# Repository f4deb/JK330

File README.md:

JK330
=====

transceiver 3-30mhz QRP

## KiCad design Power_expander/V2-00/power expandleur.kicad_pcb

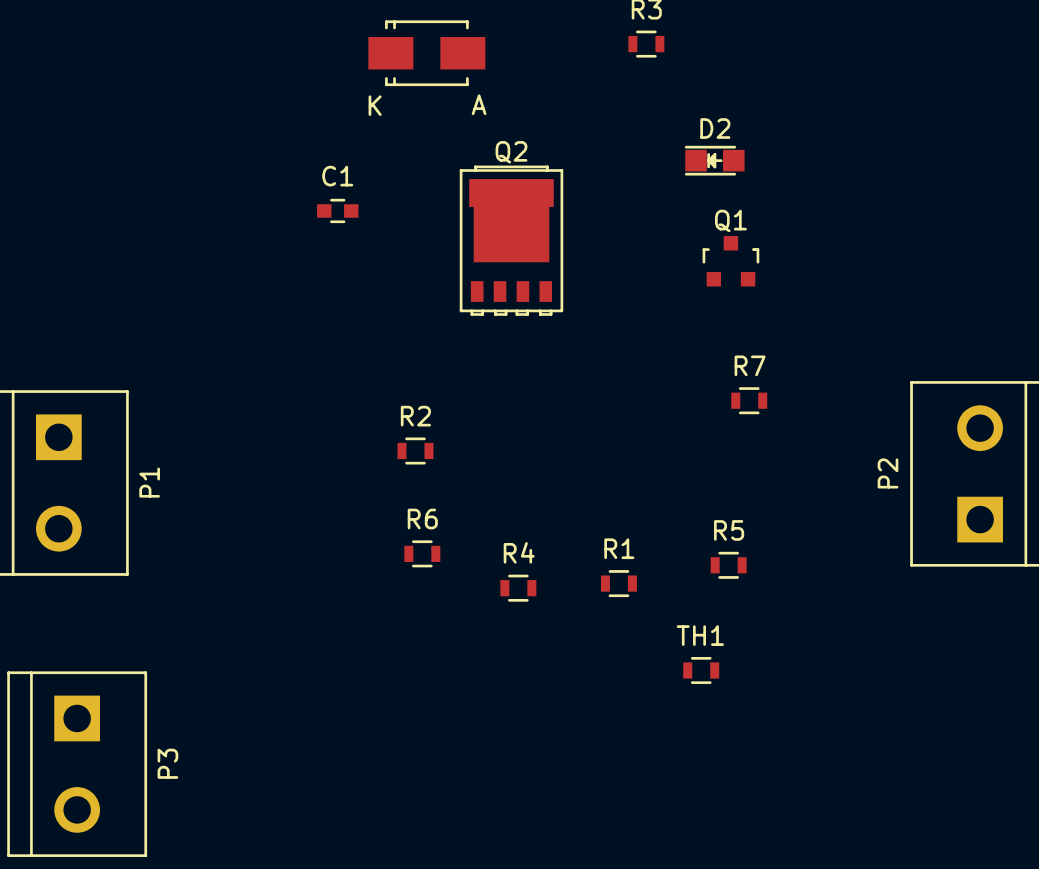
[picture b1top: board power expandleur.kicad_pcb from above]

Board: 2 copper layers, 16 parts (0 on the bottom side), 11 nets, no tracks yet.

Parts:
C1: 100nF; C_0603
D1: ZENERsmall; SMA_Standard
D2: LED; LED_0805
P1, P2, P3: CONN_01X02; bornier2
Q1: Q_NPN_BCE; SOT-23
Q2: Q_NMOS_DGS; SOT-669_LFPAK
R1: 330; R_0603
R2: 100k; R_0603
R3, R5: 1K; R_0603
R4: 10K; R_0603
R6: 4.7K; R_0603
R7: 100K; R_0603
TH1: THERMISTOR 220; R_0603

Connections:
+24V: P1.2, P3.2, R3.1
GND: C1.2, D1.2, D2.1, P1.1, Q1.3, Q2.3, R7.2
unnamed: C1.1, D1.1, R3.2, R4.1, R5.1
unnamed: D2.2, R6.2
unnamed: P2.1, R2.2
unnamed: P2.2, TH1.2
unnamed: P3.1, Q2.1
unnamed: Q1.1, R4.2
unnamed: Q1.2, Q2.2, R5.2, R6.1, R7.1
unnamed: R1.1, R2.1
unnamed: R1.2, TH1.1

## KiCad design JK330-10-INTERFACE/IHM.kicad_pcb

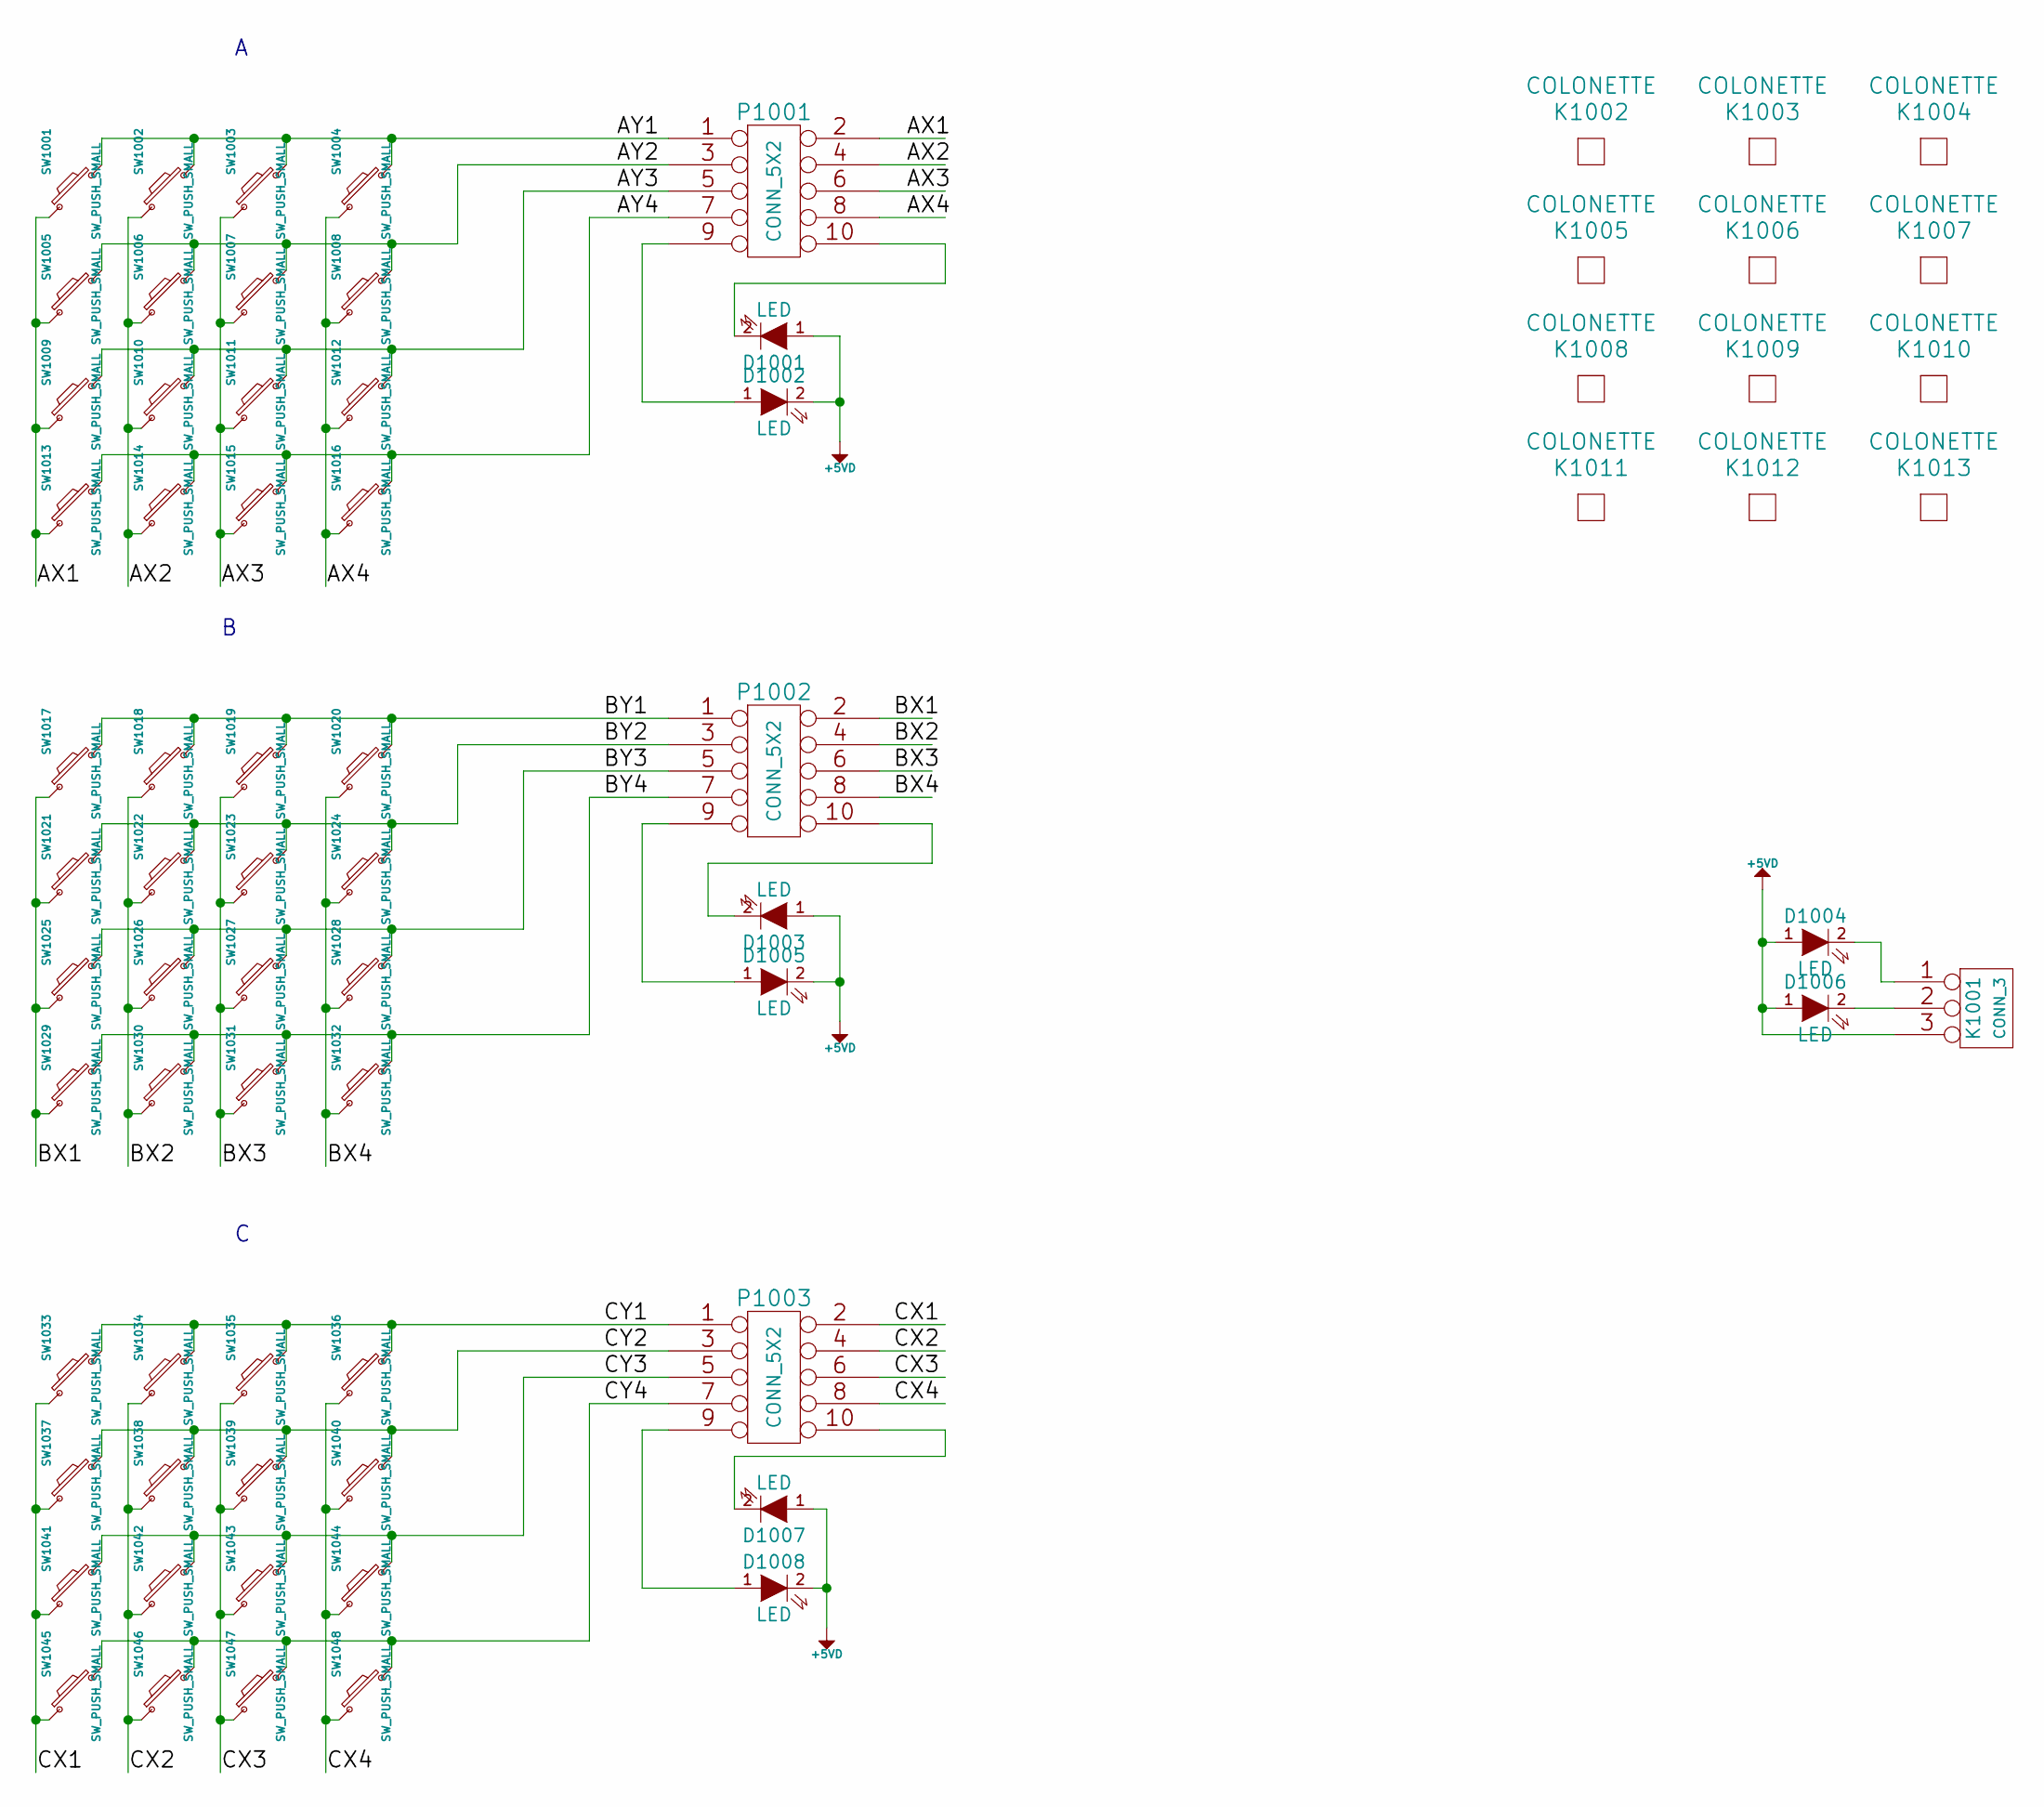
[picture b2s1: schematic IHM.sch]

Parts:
D1001, D1002, D1003, D1004, D1005, D1006, D1007, D1008: LED
K1001: CONN_3
K1002, K1003, K1004, K1005, K1006, K1007, K1008, K1009, K1010, K1011, K1012, K1013: COLONETTE
P1001, P1002, P1003: CONN_5X2
SW1001, SW1002, SW1003, SW1004, SW1005, SW1006, SW1007, SW1008, SW1009, SW1010, SW1011, SW1012, SW1013, SW1014, SW1015, SW1016, SW1017, SW1018, SW1019, SW1020, SW1021, SW1022, SW1023, SW1024, SW1025, SW1026, SW1027, SW1028, SW1029, SW1030, SW1031, SW1032, SW1033, SW1034, SW1035, SW1036, SW1037, SW1038, SW1039, SW1040, SW1041, SW1042, SW1043, SW1044, SW1045, SW1046, SW1047, SW1048: SW_PUSH_SMALL

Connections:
+5VD: D1001.1 (A), D1002.2 (K), D1003.1 (A), D1004.1 (A), D1005.2 (K), D1006.1 (A), D1007.1 (A), D1008.2 (K), K1001.3
/AX1: P1001.2, SW1001.1, SW1005.1, SW1009.1, SW1013.1
/AX2: P1001.4, SW1002.1, SW1006.1, SW1010.1, SW1014.1
/AX3: P1001.6, SW1003.1, SW1007.1, SW1011.1, SW1015.1
/AX4: P1001.8, SW1004.1, SW1008.1, SW1012.1, SW1016.1
/AY1: P1001.1, SW1001.2, SW1002.2, SW1003.2, SW1004.2
/AY2: P1001.3, SW1005.2, SW1006.2, SW1007.2, SW1008.2
/AY3: P1001.5, SW1009.2, SW1010.2, SW1011.2, SW1012.2
/AY4: P1001.7, SW1013.2, SW1014.2, SW1015.2, SW1016.2
/BX1: P1002.2, SW1017.1, SW1021.1, SW1025.1, SW1029.1
/BX2: P1002.4, SW1018.1, SW1022.1, SW1026.1, SW1030.1
/BX3: P1002.6, SW1019.1, SW1023.1, SW1027.1, SW1031.1
/BX4: P1002.8, SW1020.1, SW1024.1, SW1028.1, SW1032.1
/BY1: P1002.1, SW1017.2, SW1018.2, SW1019.2, SW1020.2
/BY2: P1002.3, SW1021.2, SW1022.2, SW1023.2, SW1024.2
/BY3: P1002.5, SW1025.2, SW1026.2, SW1027.2, SW1028.2
/BY4: P1002.7, SW1029.2, SW1030.2, SW1031.2, SW1032.2
/CX1: P1003.2, SW1033.1, SW1037.1, SW1041.1, SW1045.1
/CX2: P1003.4, SW1034.1, SW1038.1, SW1042.1, SW1046.1
/CX3: P1003.6, SW1035.1, SW1039.1, SW1043.1, SW1047.1
/CX4: P1003.8, SW1036.1, SW1040.1, SW1044.1, SW1048.1
/CY1: P1003.1, SW1033.2, SW1034.2, SW1035.2, SW1036.2
/CY2: P1003.3, SW1037.2, SW1038.2, SW1039.2, SW1040.2
/CY3: P1003.5, SW1041.2, SW1042.2, SW1043.2, SW1044.2
/CY4: P1003.7, SW1045.2, SW1046.2, SW1047.2, SW1048.2
unnamed: D1007.2 (K), P1003.10
unnamed: D1004.2 (K), K1001.1
unnamed: D1006.2 (K), K1001.2 (PM)
unnamed: D1005.1 (A), P1002.9
unnamed: D1001.2 (K), P1001.10
unnamed: D1002.1 (A), P1001.9
unnamed: D1003.2 (K), P1002.10
unnamed: D1008.1 (A), P1003.9

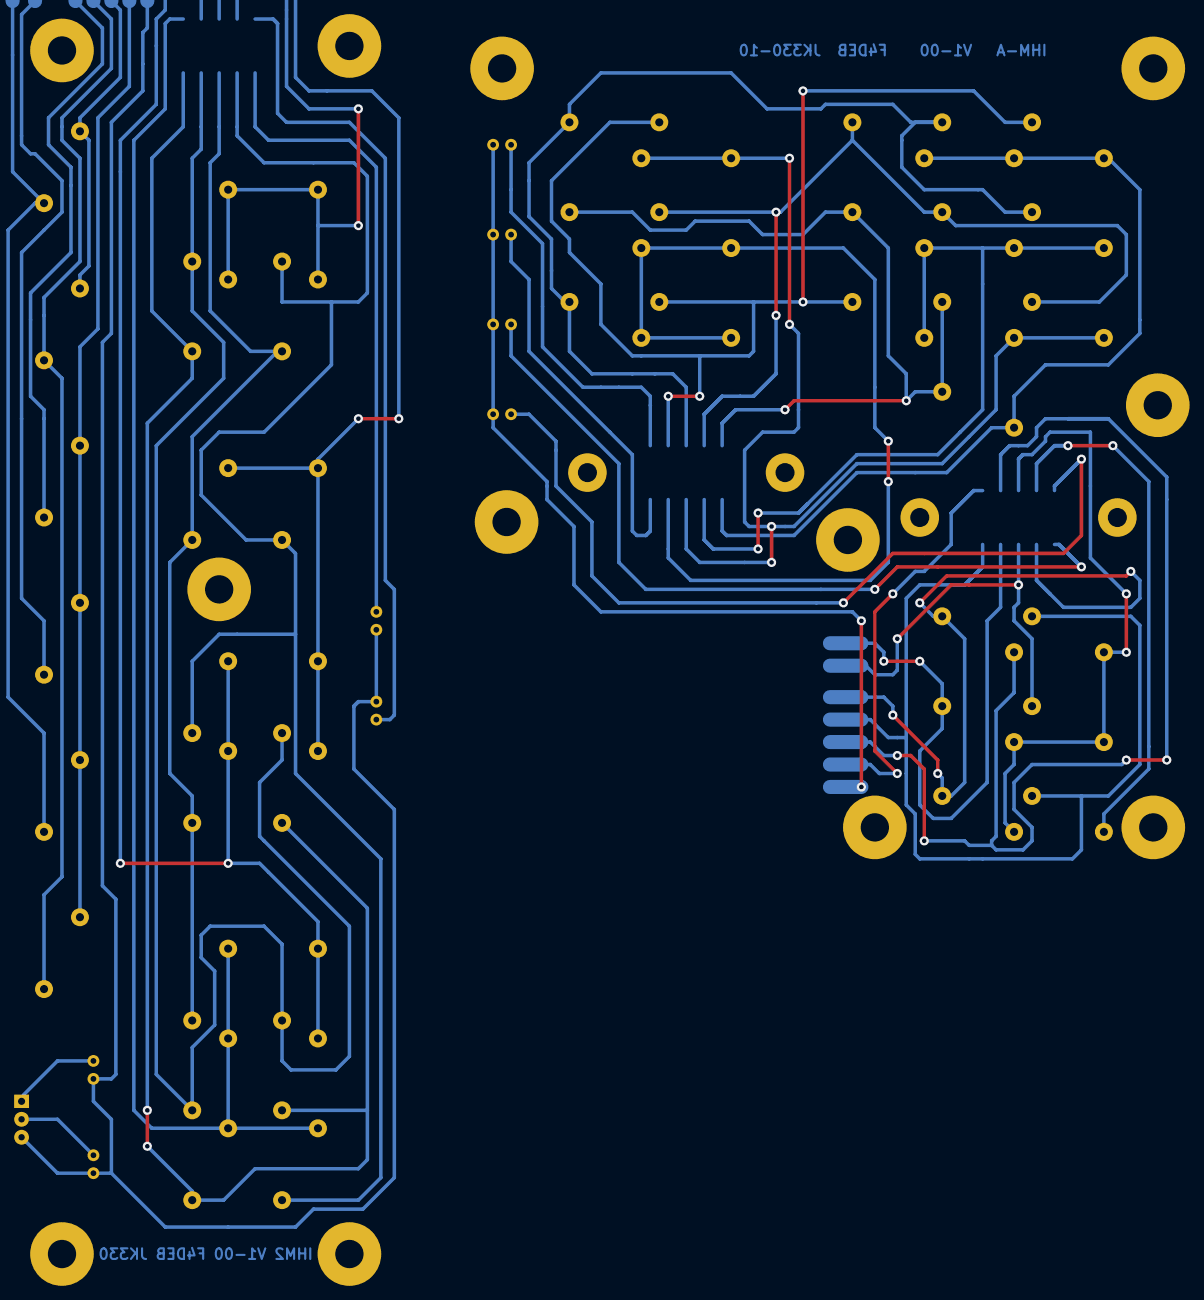
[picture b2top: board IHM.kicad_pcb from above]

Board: 2 copper layers, 68 parts (0 on the bottom side), 33 nets.

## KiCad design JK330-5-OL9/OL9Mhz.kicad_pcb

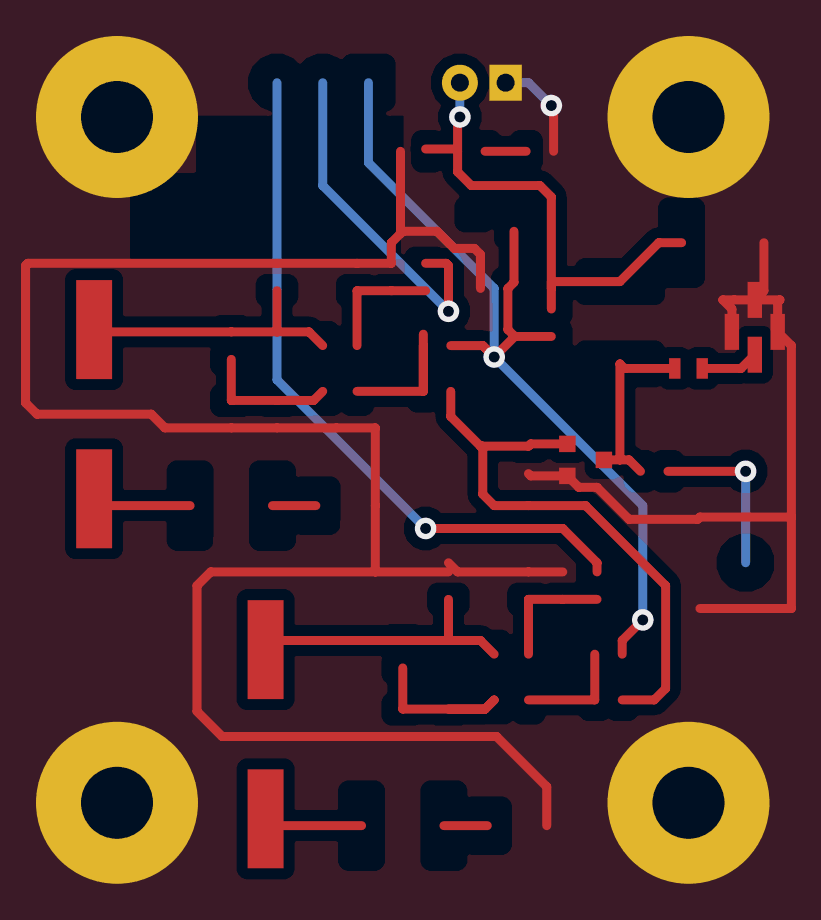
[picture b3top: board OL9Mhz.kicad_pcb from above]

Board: 2 copper layers, 10 parts (0 on the bottom side), 3 nets.

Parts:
C15: 1n; SM0603_Capa
K2: CONN_2; KK-2-HOR
K3, K4, K5, K6: COLONETTE
P2: BNC; U.FL
Q1: BSN20; SOT23EBC
X1, X2: 9Mhz; Q_49U3HMS

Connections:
GND: K2.1, K3.1, K4.1, K5.1, K6.1, P2.2, Q1.1
unnamed: C15.2, P2.1
unnamed: C15.1, Q1.3

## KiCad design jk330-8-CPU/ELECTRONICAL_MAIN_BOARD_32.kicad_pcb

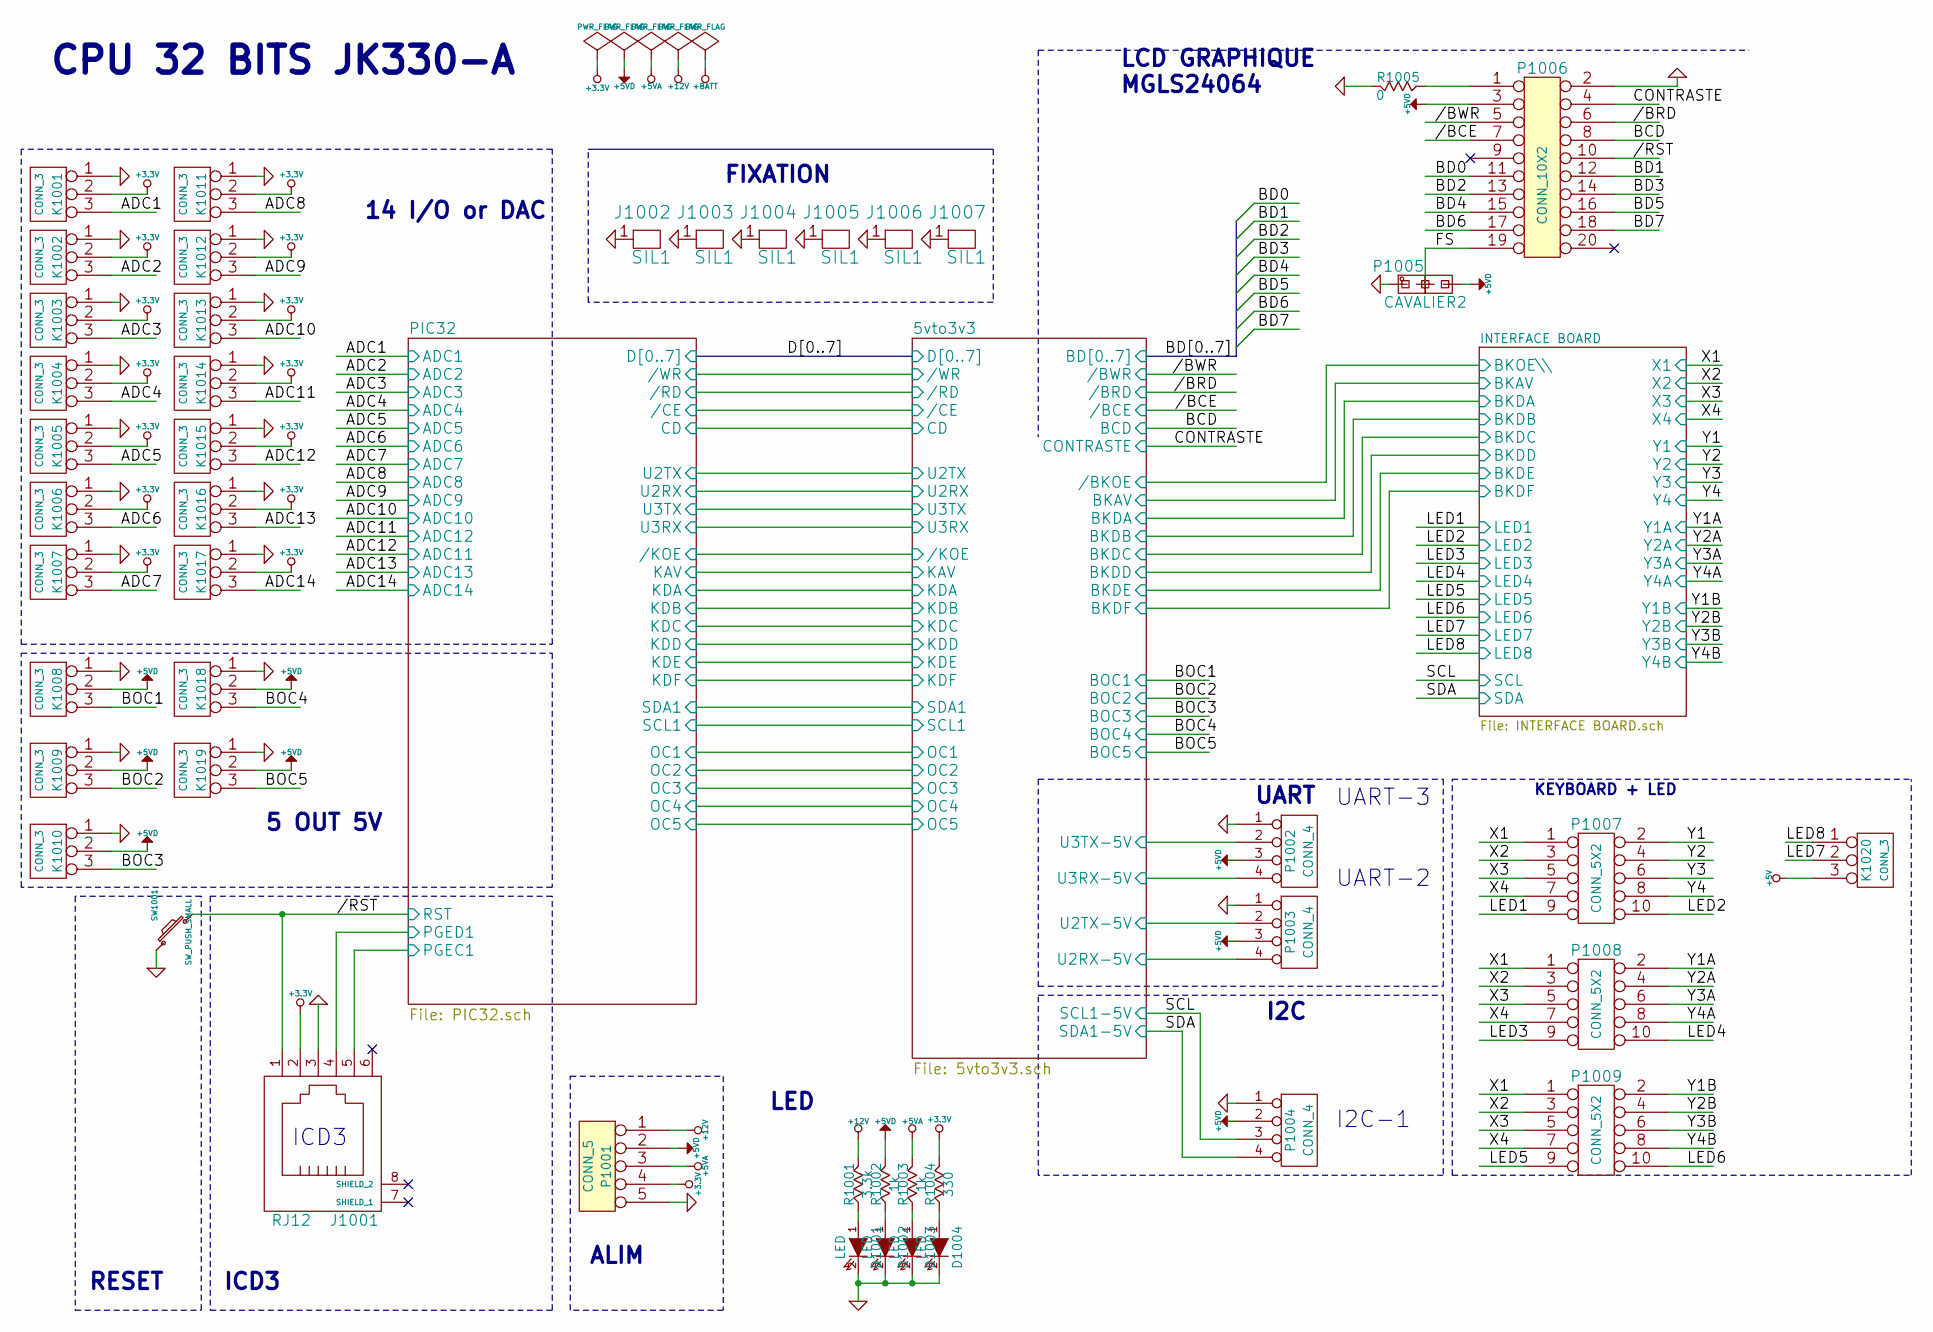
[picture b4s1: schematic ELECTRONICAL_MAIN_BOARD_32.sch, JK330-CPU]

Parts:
D1001, D1002, D1003, D1004: LED
J1001: RJ12
J1002, J1003, J1004, J1005, J1006, J1007: SIL1
K1001, K1002, K1003, K1004, K1005, K1006, K1007, K1008, K1009, K1010, K1011, K1012, K1013, K1014, K1015, K1016, K1017, K1018, K1019, K1020: CONN_3
P1001: CONN_5
P1002, P1003, P1004: CONN_4
P1005: CAVALIER2
P1006: CONN_10X2
P1007, P1008, P1009: CONN_5X2
R1001: 3.3k
R1002: 1k
R1003: 1k
R1004: 330
R1005: 0
SW1001: SW_PUSH_SMALL

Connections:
+3.3V: J1001.2, K1001.2 (PM), K1002.2 (PM), K1003.2 (PM), K1004.2 (PM), K1005.2 (PM), K1006.2 (PM), K1007.2 (PM), K1011.2 (PM), K1012.2 (PM), K1013.2 (PM), K1014.2 (PM), K1015.2 (PM), K1016.2 (PM), K1017.2 (PM), P1001.4, R1004.1; also elsewhere on the board
+5VA: P1001.3, R1003.1
+5VD: K1008.2 (PM), K1009.2 (PM), K1010.2 (PM), K1018.2 (PM), K1019.2 (PM), P1001.2, P1002.3, P1003.3, P1004.2, P1005.3, P1006.3, R1002.1; also elsewhere on the board
+12V: P1001.1, R1001.1
/5vto3v3//BCE: P1006.7; also elsewhere on the board
/5vto3v3//BRD: P1006.6; also elsewhere on the board
/5vto3v3//BWR: P1006.5; also elsewhere on the board
/5vto3v3/BCD: P1006.8; also elsewhere on the board
/5vto3v3/BOC1: K1008.3; also elsewhere on the board
/5vto3v3/BOC2: K1009.3; also elsewhere on the board
/5vto3v3/BOC3: K1010.3; also elsewhere on the board
/5vto3v3/BOC4: K1018.3; also elsewhere on the board
/5vto3v3/BOC5: K1019.3; also elsewhere on the board
/5vto3v3/CONTRASTE: P1006.4; also elsewhere on the board
/5vto3v3/U2RX-5V: P1003.4; also elsewhere on the board
/5vto3v3/U2TX-5V: P1003.2; also elsewhere on the board
/5vto3v3/U3RX-5V: P1002.4; also elsewhere on the board
/5vto3v3/U3TX-5V: P1002.2; also elsewhere on the board
/BD0: P1006.11; also elsewhere on the board
/BD1: P1006.12; also elsewhere on the board
/BD2: P1006.13; also elsewhere on the board
/BD3: P1006.14; also elsewhere on the board
/BD4: P1006.15; also elsewhere on the board
/BD5: P1006.16; also elsewhere on the board
/BD6: P1006.17; also elsewhere on the board
/BD7: P1006.18; also elsewhere on the board
/FS: P1005.2, P1006.19
/INTERFACE BOARD/LED1: P1007.9; also elsewhere on the board
/INTERFACE BOARD/LED2: P1007.10; also elsewhere on the board
/INTERFACE BOARD/LED3: P1008.9; also elsewhere on the board
/INTERFACE BOARD/LED4: P1008.10; also elsewhere on the board
/INTERFACE BOARD/LED5: P1009.9; also elsewhere on the board
/INTERFACE BOARD/LED6: P1009.10; also elsewhere on the board
/INTERFACE BOARD/LED7: K1020.2 (PM); also elsewhere on the board
/INTERFACE BOARD/LED8: K1020.1; also elsewhere on the board
/INTERFACE BOARD/SCL: P1004.3; also elsewhere on the board
/INTERFACE BOARD/SDA: P1004.4; also elsewhere on the board
/INTERFACE BOARD/X1: P1007.1, P1008.1, P1009.1; also elsewhere on the board
/INTERFACE BOARD/X2: P1007.3, P1008.3, P1009.3; also elsewhere on the board
/INTERFACE BOARD/X3: P1007.5, P1008.5, P1009.5; also elsewhere on the board
/INTERFACE BOARD/X4: P1007.7, P1008.7, P1009.7; also elsewhere on the board
/INTERFACE BOARD/Y1: P1007.2; also elsewhere on the board
/INTERFACE BOARD/Y1A: P1008.2; also elsewhere on the board
/INTERFACE BOARD/Y1B: P1009.2; also elsewhere on the board
/INTERFACE BOARD/Y2: P1007.4; also elsewhere on the board
/INTERFACE BOARD/Y2A: P1008.4; also elsewhere on the board
/INTERFACE BOARD/Y2B: P1009.4; also elsewhere on the board
/INTERFACE BOARD/Y3: P1007.6; also elsewhere on the board
/INTERFACE BOARD/Y3A: P1008.6; also elsewhere on the board
/INTERFACE BOARD/Y3B: P1009.6; also elsewhere on the board
/INTERFACE BOARD/Y4: P1007.8; also elsewhere on the board
/INTERFACE BOARD/Y4A: P1008.8; also elsewhere on the board
/INTERFACE BOARD/Y4B: P1009.8; also elsewhere on the board
/PIC32/ADC1: K1001.3; also elsewhere on the board
/PIC32/ADC2: K1002.3; also elsewhere on the board
/PIC32/ADC3: K1003.3; also elsewhere on the board
/PIC32/ADC4: K1004.3; also elsewhere on the board
/PIC32/ADC5: K1005.3; also elsewhere on the board
/PIC32/ADC6: K1006.3; also elsewhere on the board
/PIC32/ADC7: K1007.3; also elsewhere on the board
/PIC32/ADC8: K1011.3; also elsewhere on the board
/PIC32/ADC9: K1012.3; also elsewhere on the board
/PIC32/ADC10: K1013.3; also elsewhere on the board
/PIC32/ADC11: K1015.3; also elsewhere on the board
/PIC32/ADC12: K1014.3; also elsewhere on the board
/PIC32/ADC13: K1016.3; also elsewhere on the board
/PIC32/ADC14: K1017.3; also elsewhere on the board
/PIC32/PGEC1: J1001.5; also elsewhere on the board
/PIC32/PGED1: J1001.4; also elsewhere on the board
/PIC32/RST: J1001.1, P1006.10, SW1001.2; also elsewhere on the board
GND: D1001.2 (K), D1002.2 (K), D1003.2 (K), D1004.2 (K), J1001.3, J1001.7 (SHIELD_1), J1001.8 (SHIELD_2), J1002.1, J1003.1, J1004.1, J1005.1, J1006.1, J1007.1, K1001.1, K1002.1, K1003.1, K1004.1, K1005.1, K1006.1, K1007.1, K1008.1, K1009.1, K1010.1, K1011.1, K1012.1, K1013.1, K1014.1, K1015.1, K1016.1, K1017.1, K1018.1, K1019.1, P1001.5, P1002.1, P1003.1, P1004.1, P1005.1, P1006.2, R1005.1, SW1001.1; also elsewhere on the board
unnamed: D1003.1 (A), R1003.2
unnamed: P1006.1, R1005.2
unnamed: D1001.1 (A), R1001.2
unnamed: D1004.1 (A), R1004.2
unnamed: D1002.1 (A), R1002.2

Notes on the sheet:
ALIM
LED
CPU 32 BITS JK330-A
LCD GRAPHIQUE MGLS24064
ICD3
UART
I2C
I2C-1
UART-3
FIXATION
UART-2
RESET
KEYBOARD + LED
5 OUT 5V
14 I/O or DAC

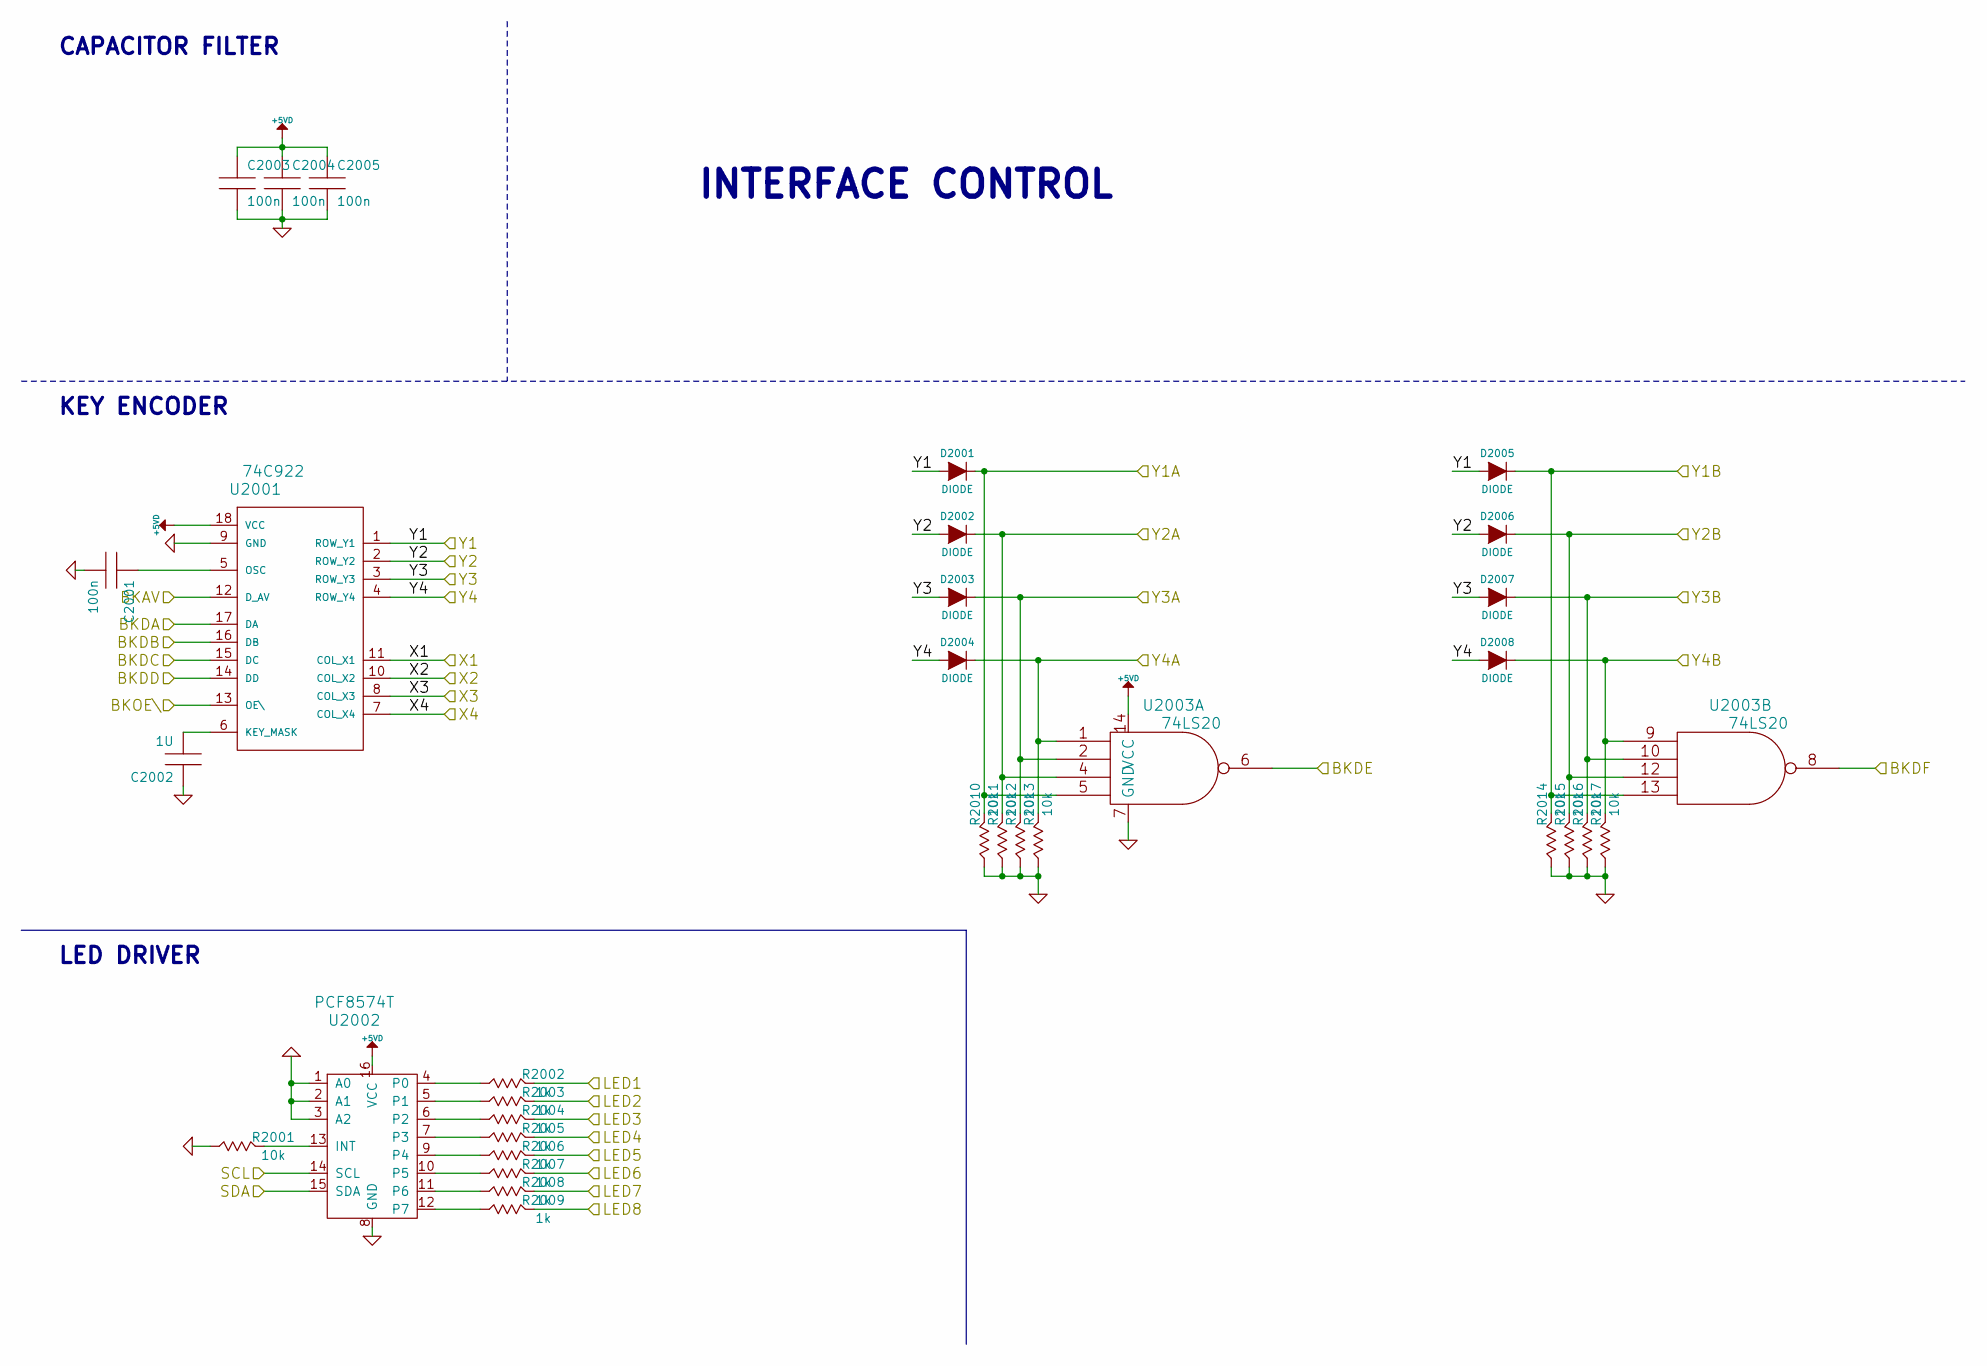
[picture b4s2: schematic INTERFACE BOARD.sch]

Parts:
C2001, C2003, C2004, C2005: 100n
C2002: 1U
D2001, D2002, D2003, D2004, D2005, D2006, D2007, D2008: DIODE
R2001, R2010, R2011, R2012, R2013, R2014, R2015, R2016, R2017: 10k
R2002, R2003, R2004, R2005, R2006, R2007, R2008, R2009: 1k
U2001: 74C922
U2002: PCF8574T
U2003: 74LS20

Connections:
+5VD: C2003.1, C2004.1, C2005.1, U2001.18 (VCC), U2002.16 (VCC), U2003.14 (VCC); also elsewhere on the board
/5vto3v3//BKOE: U2001.13 (OE\); also elsewhere on the board
/5vto3v3/BKAV: U2001.12 (D_AV); also elsewhere on the board
/5vto3v3/BKDA: U2001.17 (DA); also elsewhere on the board
/5vto3v3/BKDB: U2001.16 (DB); also elsewhere on the board
/5vto3v3/BKDC: U2001.15 (DC); also elsewhere on the board
/5vto3v3/BKDD: U2001.14 (DD); also elsewhere on the board
/5vto3v3/BKDE: U2003.6; also elsewhere on the board
/5vto3v3/BKDF: U2003.8; also elsewhere on the board
/INTERFACE BOARD/LED1: R2002.1; also elsewhere on the board
/INTERFACE BOARD/LED2: R2003.1; also elsewhere on the board
/INTERFACE BOARD/LED3: R2004.1; also elsewhere on the board
/INTERFACE BOARD/LED4: R2005.1; also elsewhere on the board
/INTERFACE BOARD/LED5: R2006.1; also elsewhere on the board
/INTERFACE BOARD/LED6: R2007.1; also elsewhere on the board
/INTERFACE BOARD/LED7: R2008.1; also elsewhere on the board
/INTERFACE BOARD/LED8: R2009.1; also elsewhere on the board
/INTERFACE BOARD/SCL: U2002.14 (SCL); also elsewhere on the board
/INTERFACE BOARD/SDA: U2002.15 (SDA); also elsewhere on the board
/INTERFACE BOARD/X1: U2001.11 (COL_X1); also elsewhere on the board
/INTERFACE BOARD/X2: U2001.10 (COL_X2); also elsewhere on the board
/INTERFACE BOARD/X3: U2001.8 (COL_X3); also elsewhere on the board
/INTERFACE BOARD/X4: U2001.7 (COL_X4); also elsewhere on the board
/INTERFACE BOARD/Y1: D2001.1 (A), D2005.1 (A), U2001.1 (ROW_Y1); also elsewhere on the board
/INTERFACE BOARD/Y1A: D2001.2 (K), R2010.1, U2003.5; also elsewhere on the board
/INTERFACE BOARD/Y1B: D2005.2 (K), R2014.1, U2003.13; also elsewhere on the board
/INTERFACE BOARD/Y2: D2002.1 (A), D2006.1 (A), U2001.2 (ROW_Y2); also elsewhere on the board
/INTERFACE BOARD/Y2A: D2002.2 (K), R2011.1, U2003.4; also elsewhere on the board
/INTERFACE BOARD/Y2B: D2006.2 (K), R2015.1, U2003.12; also elsewhere on the board
/INTERFACE BOARD/Y3: D2003.1 (A), D2007.1 (A), U2001.3 (ROW_Y3); also elsewhere on the board
/INTERFACE BOARD/Y3A: D2003.2 (K), R2012.1, U2003.2; also elsewhere on the board
/INTERFACE BOARD/Y3B: D2007.2 (K), R2016.1, U2003.10; also elsewhere on the board
/INTERFACE BOARD/Y4: D2004.1 (A), D2008.1 (A), U2001.4 (ROW_Y4); also elsewhere on the board
/INTERFACE BOARD/Y4A: D2004.2 (K), R2013.1, U2003.1; also elsewhere on the board
/INTERFACE BOARD/Y4B: D2008.2 (K), R2017.1, U2003.9; also elsewhere on the board
GND: C2001.2, C2002.1, C2003.2, C2004.2, C2005.2, R2001.2, R2010.2, R2011.2, R2012.2, R2013.2, R2014.2, R2015.2, R2016.2, R2017.2, U2001.9 (GND), U2002.1 (A0), U2002.2 (A1), U2002.3 (A2), U2002.8 (GND), U2003.7 (GND); also elsewhere on the board
unnamed: C2001.1, U2001.5 (OSC)
unnamed: C2002.2, U2001.6 (KEY_MASK)
unnamed: R2001.1, U2002.13 (INT)
unnamed: R2003.2, U2002.5 (P1)
unnamed: R2008.2, U2002.11 (P6)
unnamed: R2006.2, U2002.9 (P4)
unnamed: R2004.2, U2002.6 (P2)
unnamed: R2002.2, U2002.4 (P0)
unnamed: R2005.2, U2002.7 (P3)
unnamed: R2007.2, U2002.10 (P5)
unnamed: R2009.2, U2002.12 (P7)

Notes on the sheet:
CAPACITOR FILTER
KEY ENCODER
LED DRIVER
INTERFACE CONTROL
